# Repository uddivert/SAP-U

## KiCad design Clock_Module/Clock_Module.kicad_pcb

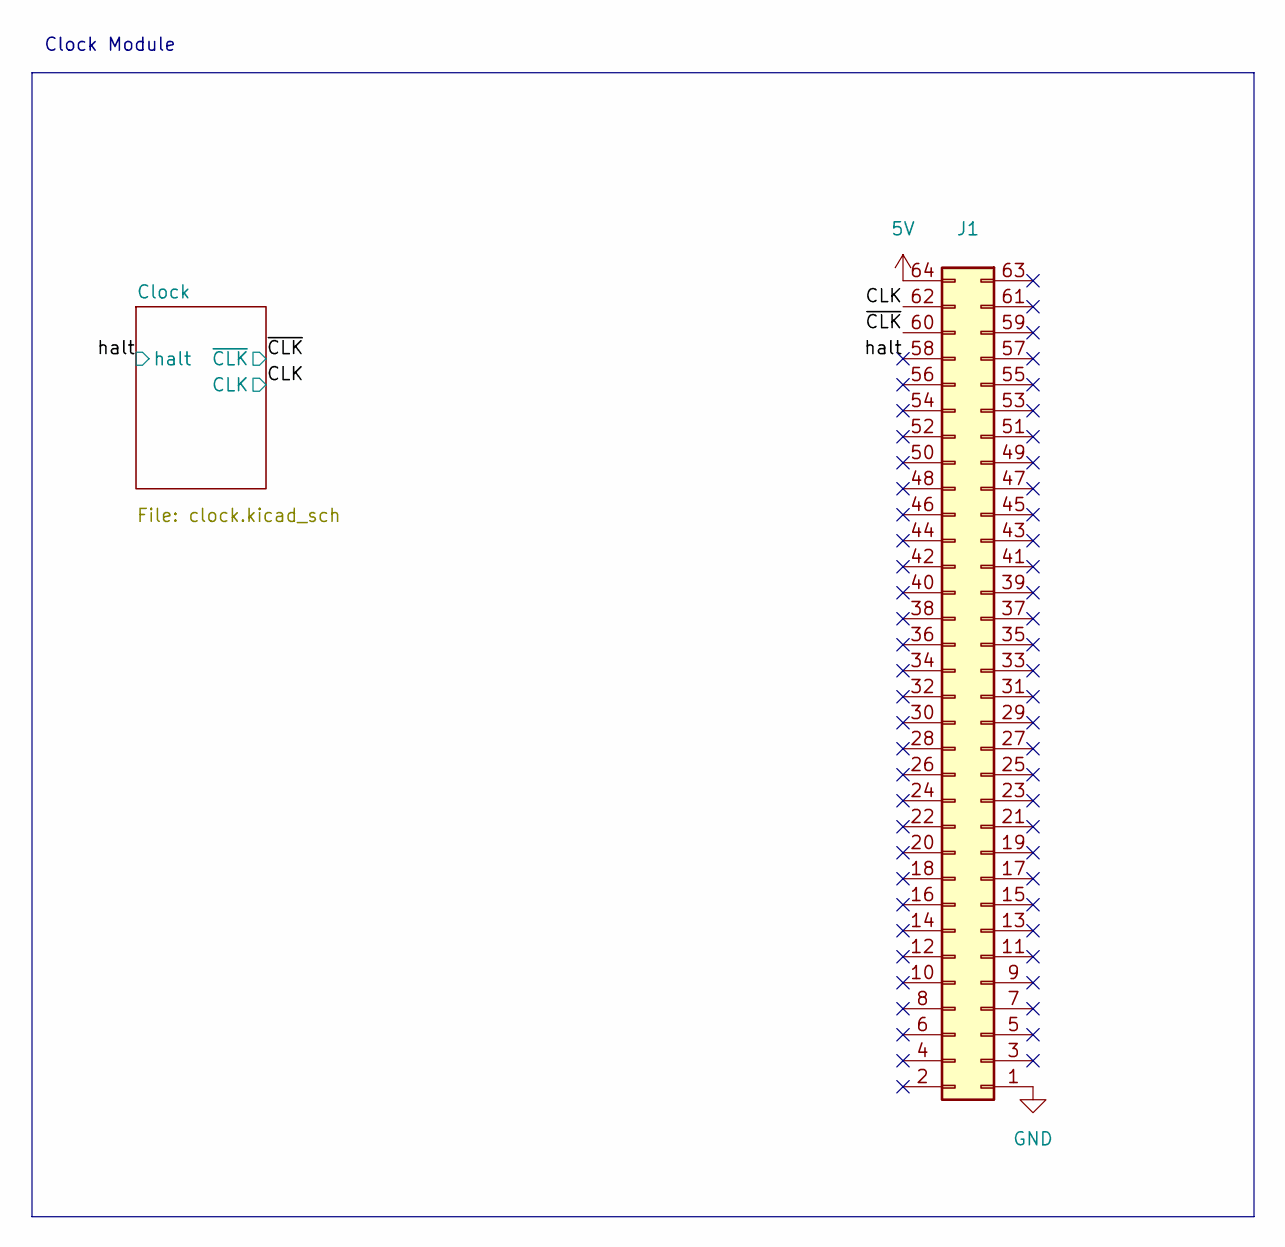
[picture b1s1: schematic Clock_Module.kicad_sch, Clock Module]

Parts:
J1: PC104-Standard

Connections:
5V: J1.64; also elsewhere on the board
/CLK: J1.62; also elsewhere on the board
/halt: J1.58; also elsewhere on the board
/~CLK: J1.60; also elsewhere on the board
GND: J1.1; also elsewhere on the board

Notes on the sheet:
Clock Module

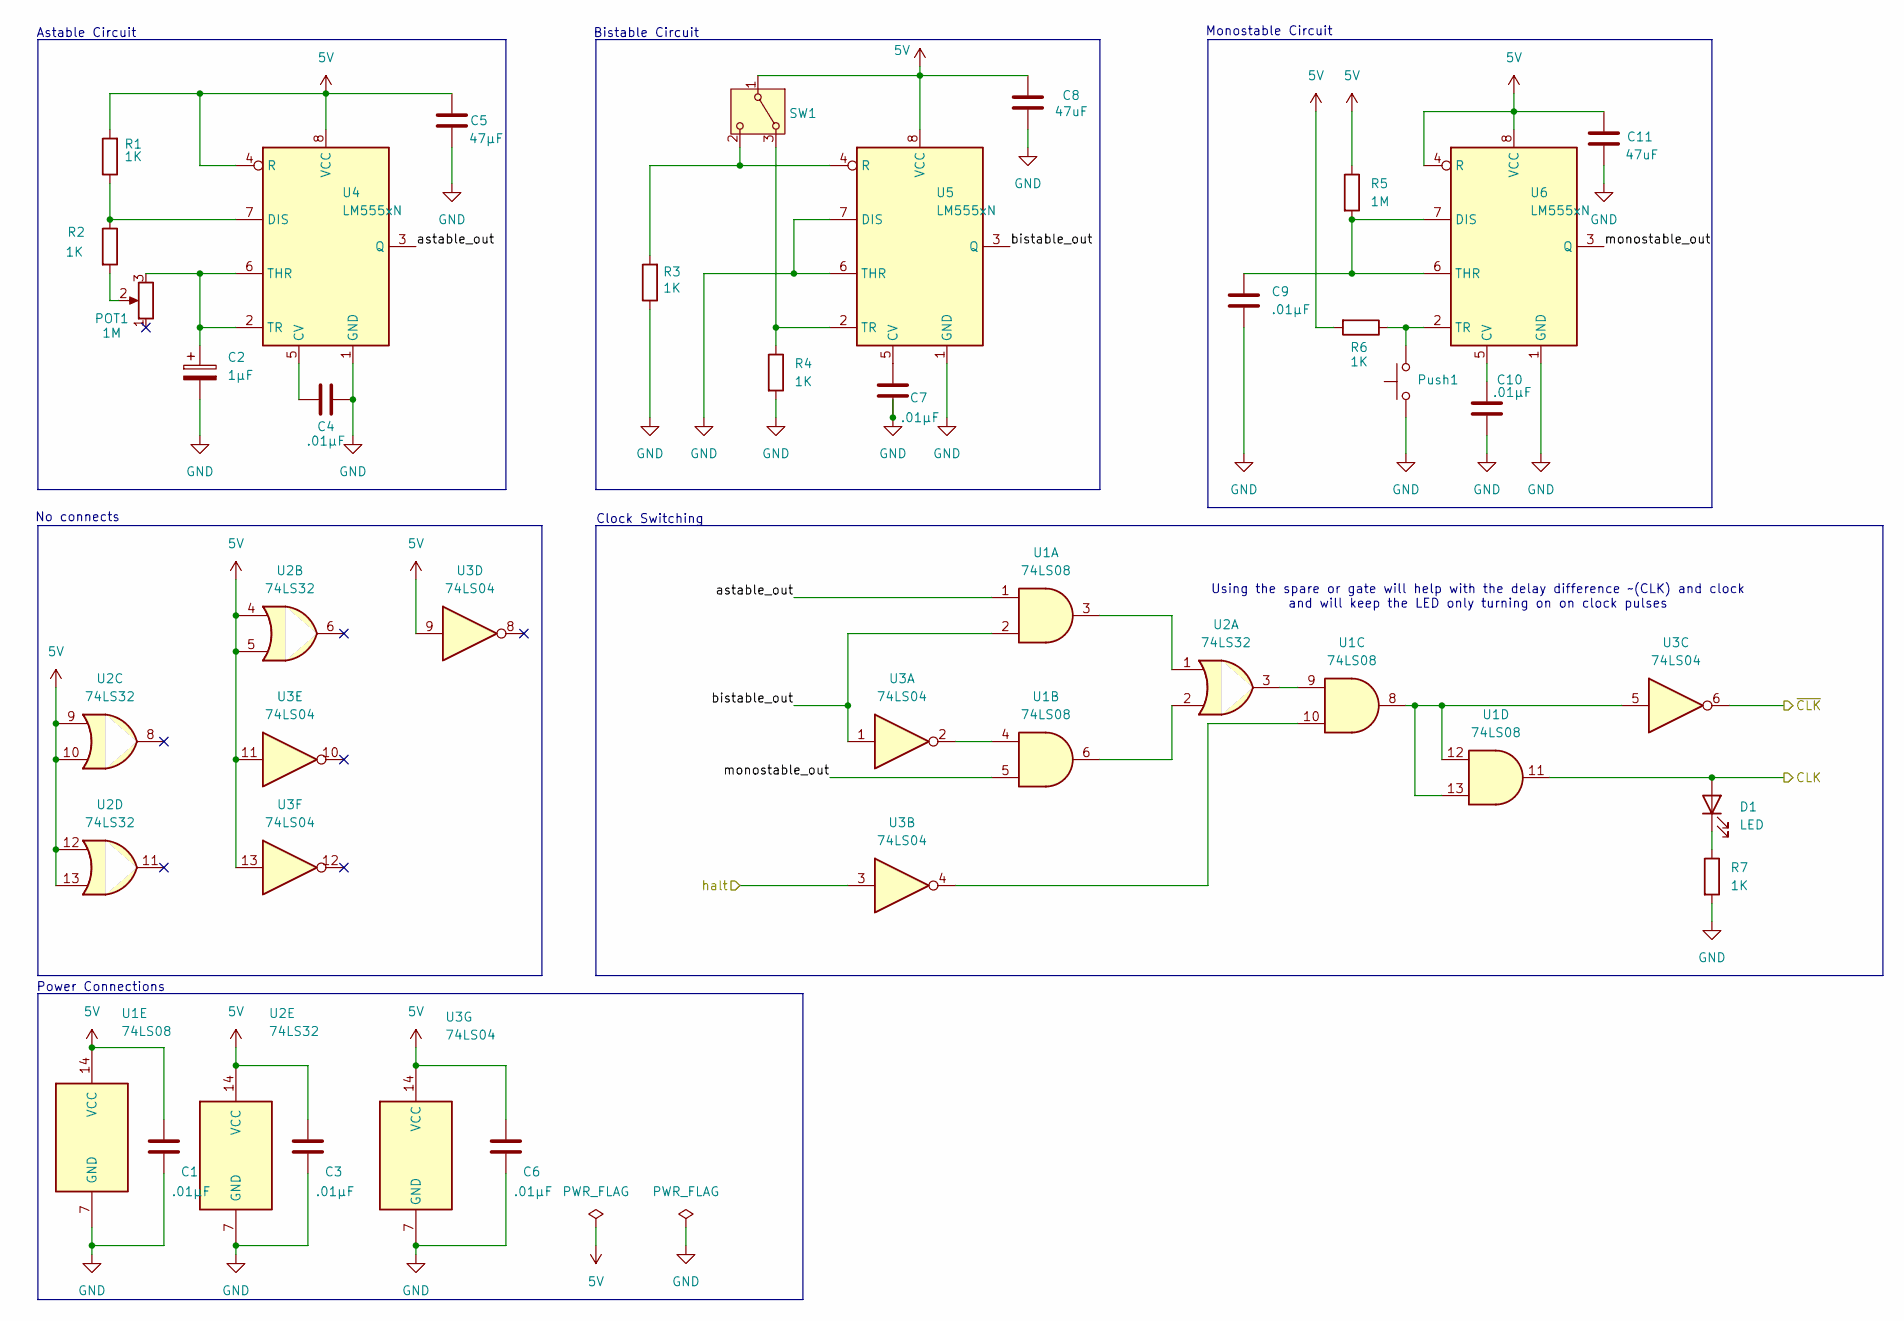
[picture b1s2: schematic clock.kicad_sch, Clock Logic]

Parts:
C1, C3, C4, C6, C7, C9, C10: .01µF; C_Disc_D5.0mm_W2.5mm_P2.50mm
C2: 1µF; C_Radial_D5.0mm_H11.0mm_P2.00mm
C5: 47µF; C_Disc_D5.0mm_W2.5mm_P2.50mm
C8, C11: 47uF; C_Disc_D5.0mm_W2.5mm_P2.50mm
D1: LED; LED_D5.0mm
POT1: 1M; Potentiometer_Bourns_3266Y_Vertical
Push1: SW_Push; SW_PUSH_6mm_H4.3mm
R1, R2, R3, R4, R6, R7: 1K; R_Axial_DIN0207_L6.3mm_D2.5mm_P5.08mm_Vertical
R5: 1M; R_Axial_DIN0207_L6.3mm_D2.5mm_P5.08mm_Vertical
SW1: Switch; SW_Slide-Jameco-SS-12E17-G020
U1: 74LS08; SN74LS08N
U2: 74LS32; SN74LS32N
U3: 74LS04; SN74LS04N
U4, U5, U6: LM555xN; DIP-8_W7.62mm

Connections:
5V: C1.2, C3.2, C5.1, C6.2, C8.2, C11.1, R1.2, R5.1, R6.2, SW1.1 (B), U1.14 (VCC), U2.4, U2.5, U2.9, U2.10, U2.12, U2.13, U2.14 (VCC), U3.9, U3.11, U3.13, U3.14 (VCC), U4.4 (R), U4.8 (VCC), U5.8 (VCC), U6.4 (R), U6.8 (VCC); also elsewhere on the board
/CLK: D1.2 (A), U1.11; also elsewhere on the board
/Clock/astable_out: U1.1, U4.3 (Q)
/Clock/bistable_out: U1.2, U3.1, U5.3 (Q)
/Clock/monostable_out: U1.5, U6.3 (Q)
/halt: U3.3; also elsewhere on the board
/~CLK: U3.6; also elsewhere on the board
GND: C1.1, C2.2, C3.1, C4.1, C5.2, C6.1, C7.1, C8.1, C9.1, C10.1, C11.2, Push1.1, R3.1, R4.2, R7.2, U1.7 (GND), U2.7 (GND), U3.7 (GND), U4.1 (GND), U5.1 (GND), U5.6 (THR), U5.7 (DIS), U6.1 (GND); also elsewhere on the board
unnamed: D1.1 (K), R7.1
unnamed: POT1.2, R2.2
unnamed: R4.1, SW1.3 (A), U5.2 (TR)
unnamed: R3.2, SW1.2 (C), U5.4 (R)
unnamed: U1.3, U2.1
unnamed: U1.4, U3.2
unnamed: U1.6, U2.2
unnamed: U1.9, U2.3
unnamed: U1.10, U3.4
unnamed: U1.8, U1.12, U1.13, U3.5
unnamed: C4.2, U4.5 (CV)
unnamed: R1.1, R2.1, U4.7 (DIS)
unnamed: C2.1, POT1.3, U4.2 (TR), U4.6 (THR)
unnamed: C7.2, U5.5 (CV)
unnamed: C10.2, U6.5 (CV)
unnamed: C9.2, R5.2, U6.6 (THR), U6.7 (DIS)
unnamed: Push1.2, R6.1, U6.2 (TR)

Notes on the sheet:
Astable Circuit
Power Connections
Bistable Circuit
Monostable Circuit
Clock Switching
No connects
Using the spare or gate will help with the delay difference ~(CLK) and clock and will keep the LED only turning on on clock pulses

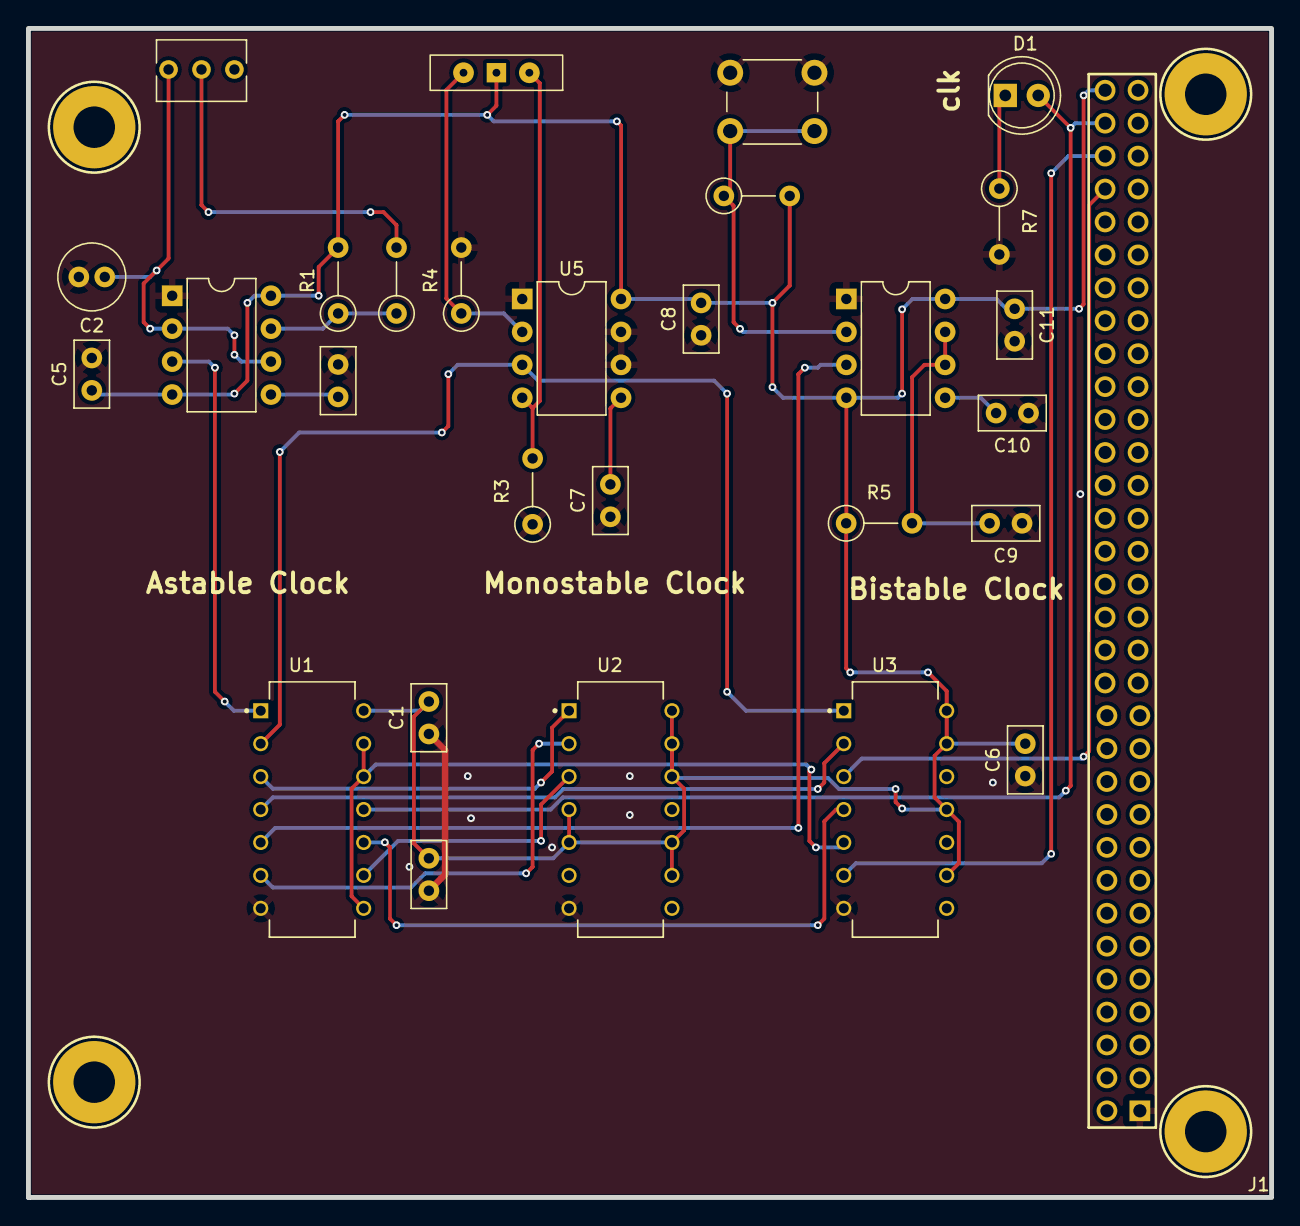
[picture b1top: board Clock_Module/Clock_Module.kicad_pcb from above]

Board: 2 copper layers, 95.9 x 90.2 mm, 29 parts (0 on the bottom side), 25 nets.

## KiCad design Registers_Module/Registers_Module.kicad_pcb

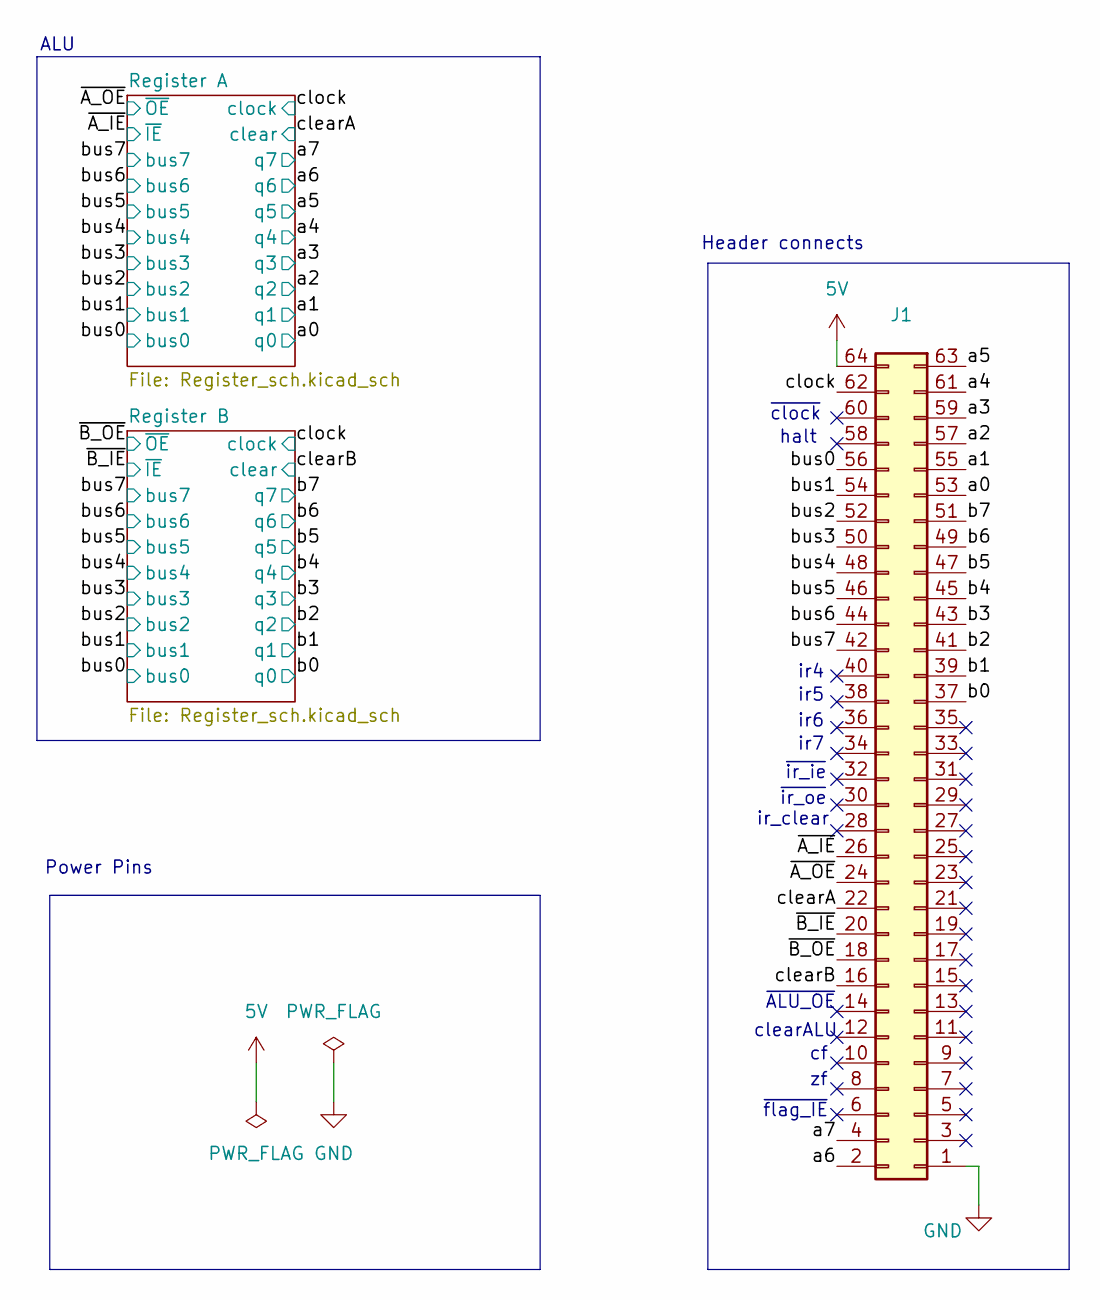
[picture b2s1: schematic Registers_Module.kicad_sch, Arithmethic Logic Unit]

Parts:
J1: PC104-Standard

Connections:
5V: J1.64; also elsewhere on the board
/a0: J1.53; also elsewhere on the board
/a1: J1.55; also elsewhere on the board
/a2: J1.57; also elsewhere on the board
/a3: J1.59; also elsewhere on the board
/a4: J1.61; also elsewhere on the board
/a5: J1.63; also elsewhere on the board
/a6: J1.2; also elsewhere on the board
/a7: J1.4; also elsewhere on the board
/b0: J1.37; also elsewhere on the board
/b1: J1.39; also elsewhere on the board
/b2: J1.41; also elsewhere on the board
/b3: J1.43; also elsewhere on the board
/b4: J1.45; also elsewhere on the board
/b5: J1.47; also elsewhere on the board
/b6: J1.49; also elsewhere on the board
/b7: J1.51; also elsewhere on the board
/bus0: J1.56; also elsewhere on the board
/bus1: J1.54; also elsewhere on the board
/bus2: J1.52; also elsewhere on the board
/bus3: J1.50; also elsewhere on the board
/bus4: J1.48; also elsewhere on the board
/bus5: J1.46; also elsewhere on the board
/bus6: J1.44; also elsewhere on the board
/bus7: J1.42; also elsewhere on the board
/clearA: J1.22; also elsewhere on the board
/clearB: J1.16; also elsewhere on the board
/clock: J1.62; also elsewhere on the board
/~A_IE: J1.26; also elsewhere on the board
/~A_OE: J1.24; also elsewhere on the board
/~B_IE: J1.20; also elsewhere on the board
/~B_OE: J1.18; also elsewhere on the board
GND: J1.1; also elsewhere on the board

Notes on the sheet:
ir5
ir6
~{ir_ie}
ALU
~{ir_oe}
~{ALU_OE}
ir_clear
halt
~{clock}
ir7
ir4
Header connects
Power Pins
~{flag_IE}
clearALU

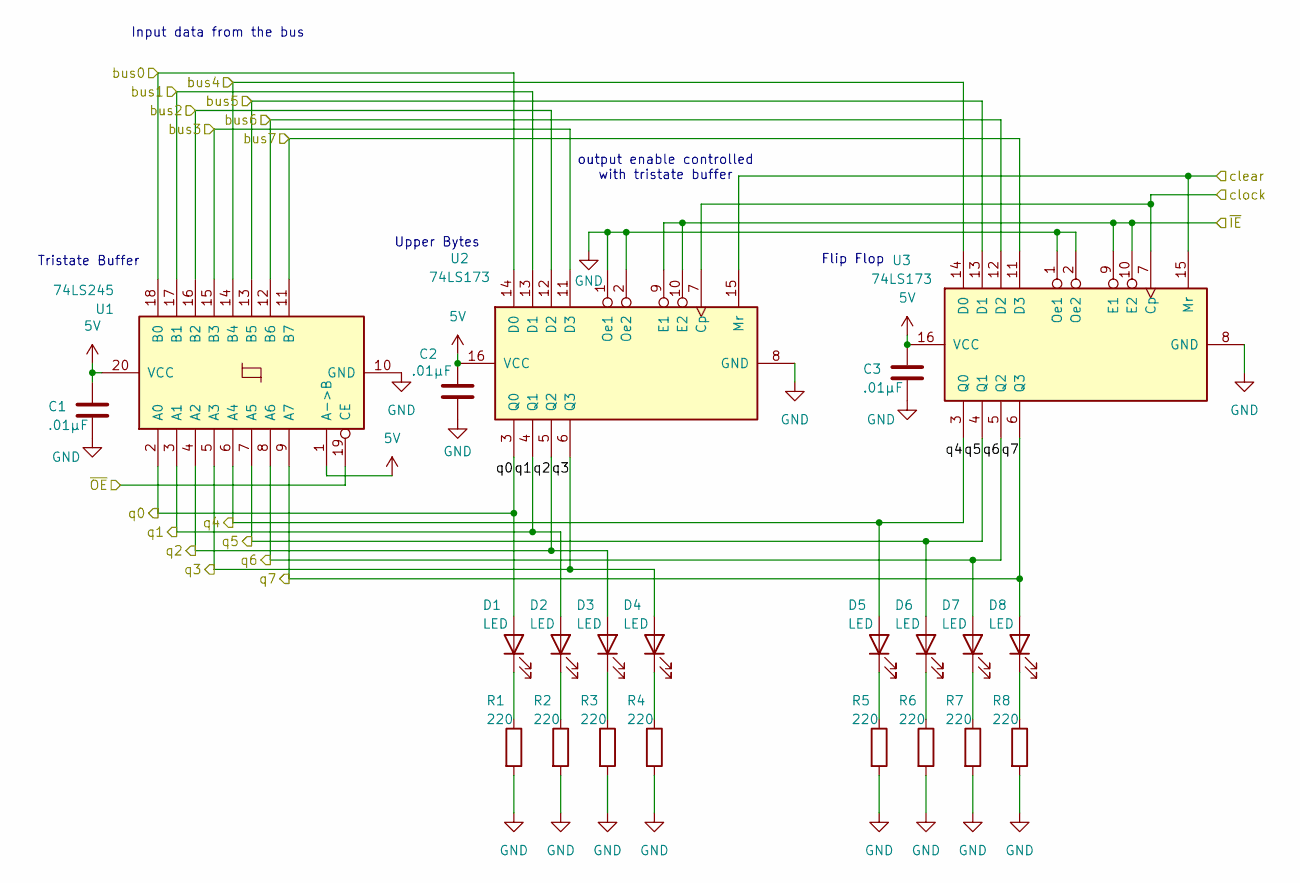
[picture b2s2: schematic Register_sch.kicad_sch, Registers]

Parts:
C1, C2, C3: .01µF; C_Disc_D5.0mm_W2.5mm_P2.50mm
D1, D2, D3, D4, D5, D6, D7, D8: LED; LED_D5.0mm
R1, R2, R3, R4, R5, R6, R7, R8: 220; R_Axial_DIN0207_L6.3mm_D2.5mm_P5.08mm_Vertical
U1: 74LS245; DIP-20_W7.62mm
U2, U3: 74LS173; DIP-16_W7.62mm

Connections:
5V: C1.2, C2.2, C3.2, U1.1 (A->B), U1.20 (VCC), U2.16 (VCC), U3.16 (VCC); also elsewhere on the board
/a0: D1.2 (A), U1.2 (A0), U2.3 (Q0); also elsewhere on the board
/a1: D2.2 (A), U1.3 (A1), U2.4 (Q1); also elsewhere on the board
/a2: D3.2 (A), U1.4 (A2), U2.5 (Q2); also elsewhere on the board
/a3: D4.2 (A), U1.5 (A3), U2.6 (Q3); also elsewhere on the board
/a4: D5.2 (A), U1.6 (A4), U3.3 (Q0); also elsewhere on the board
/a5: D6.2 (A), U1.7 (A5), U3.4 (Q1); also elsewhere on the board
/a6: D7.2 (A), U1.8 (A6), U3.5 (Q2); also elsewhere on the board
/a7: D8.2 (A), U1.9 (A7), U3.6 (Q3); also elsewhere on the board
/bus0: U1.18 (B0), U2.14 (D0); also elsewhere on the board
/bus1: U1.17 (B1), U2.13 (D1); also elsewhere on the board
/bus2: U1.16 (B2), U2.12 (D2); also elsewhere on the board
/bus3: U1.15 (B3), U2.11 (D3); also elsewhere on the board
/bus4: U1.14 (B4), U3.14 (D0); also elsewhere on the board
/bus5: U1.13 (B5), U3.13 (D1); also elsewhere on the board
/bus6: U1.12 (B6), U3.12 (D2); also elsewhere on the board
/bus7: U1.11 (B7), U3.11 (D3); also elsewhere on the board
/clearA: U2.15 (Mr), U3.15 (Mr); also elsewhere on the board
/clock: U2.7 (Cp), U3.7 (Cp); also elsewhere on the board
/~A_IE: U2.9 (E1), U2.10 (E2), U3.9 (E1), U3.10 (E2); also elsewhere on the board
/~A_OE: U1.19 (CE); also elsewhere on the board
GND: C1.1, C2.1, C3.1, R1.2, R2.2, R3.2, R4.2, R5.2, R6.2, R7.2, R8.2, U1.10 (GND), U2.1 (Oe1), U2.2 (Oe2), U2.8 (GND), U3.1 (Oe1), U3.2 (Oe2), U3.8 (GND); also elsewhere on the board
unnamed: D1.1 (K), R1.1
unnamed: D2.1 (K), R2.1
unnamed: D3.1 (K), R3.1
unnamed: D4.1 (K), R4.1
unnamed: D5.1 (K), R5.1
unnamed: D6.1 (K), R6.1
unnamed: D7.1 (K), R7.1
unnamed: D8.1 (K), R8.1

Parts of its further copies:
C12, C13, C14: .01µF; C_Disc_D5.0mm_W2.5mm_P2.50mm
D17, D18, D19, D20, D21, D22, D23, D24: LED; LED_D5.0mm
R17, R18, R19, R20, R21, R22, R23, R24: 220; R_Axial_DIN0207_L6.3mm_D2.5mm_P5.08mm_Vertical
U12: 74LS245; DIP-20_W7.62mm
U13, U14: 74LS173; DIP-16_W7.62mm

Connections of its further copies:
5V: C12.2, C13.2, C14.2, U12.1 (A->B), U12.20 (VCC), U13.16 (VCC), U14.16 (VCC); also elsewhere on the board
/b0: D17.2 (A), U12.2 (A0), U13.3 (Q0); also elsewhere on the board
/b1: D18.2 (A), U12.3 (A1), U13.4 (Q1); also elsewhere on the board
/b2: D19.2 (A), U12.4 (A2), U13.5 (Q2); also elsewhere on the board
/b3: D20.2 (A), U12.5 (A3), U13.6 (Q3); also elsewhere on the board
/b4: D21.2 (A), U12.6 (A4), U14.3 (Q0); also elsewhere on the board
/b5: D22.2 (A), U12.7 (A5), U14.4 (Q1); also elsewhere on the board
/b6: D23.2 (A), U12.8 (A6), U14.5 (Q2); also elsewhere on the board
/b7: D24.2 (A), U12.9 (A7), U14.6 (Q3); also elsewhere on the board
/bus0: U12.18 (B0), U13.14 (D0); also elsewhere on the board
/bus1: U12.17 (B1), U13.13 (D1); also elsewhere on the board
/bus2: U12.16 (B2), U13.12 (D2); also elsewhere on the board
/bus3: U12.15 (B3), U13.11 (D3); also elsewhere on the board
/bus4: U12.14 (B4), U14.14 (D0); also elsewhere on the board
/bus5: U12.13 (B5), U14.13 (D1); also elsewhere on the board
/bus6: U12.12 (B6), U14.12 (D2); also elsewhere on the board
/bus7: U12.11 (B7), U14.11 (D3); also elsewhere on the board
/clearB: U13.15 (Mr), U14.15 (Mr); also elsewhere on the board
/clock: U13.7 (Cp), U14.7 (Cp); also elsewhere on the board
/~B_IE: U13.9 (E1), U13.10 (E2), U14.9 (E1), U14.10 (E2); also elsewhere on the board
/~B_OE: U12.19 (CE); also elsewhere on the board
GND: C12.1, C13.1, C14.1, R17.2, R18.2, R19.2, R20.2, R21.2, R22.2, R23.2, R24.2, U12.10 (GND), U13.1 (Oe1), U13.2 (Oe2), U13.8 (GND), U14.1 (Oe1), U14.2 (Oe2), U14.8 (GND); also elsewhere on the board
unnamed: D17.1 (K), R17.1
unnamed: D18.1 (K), R18.1
unnamed: D19.1 (K), R19.1
unnamed: D20.1 (K), R20.1
unnamed: D21.1 (K), R21.1
unnamed: D22.1 (K), R22.1
unnamed: D23.1 (K), R23.1
unnamed: D24.1 (K), R24.1

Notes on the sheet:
Upper Bytes
Flip Flop
output enable controlled with tristate buffer
Input data from the bus
Tristate Buffer

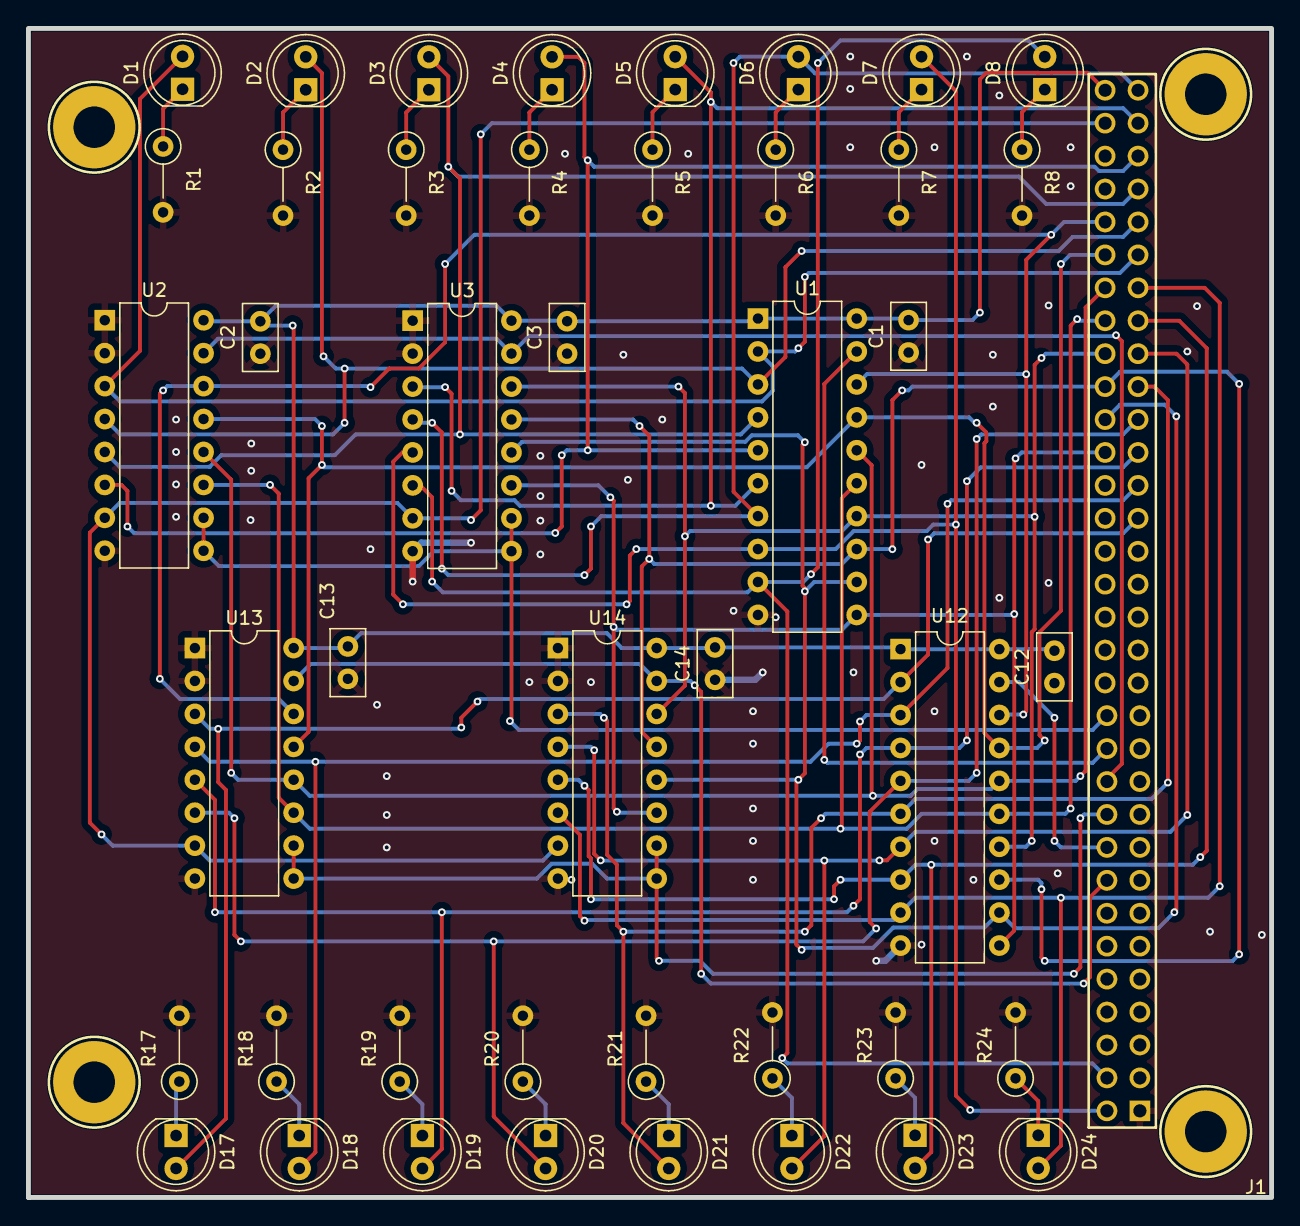
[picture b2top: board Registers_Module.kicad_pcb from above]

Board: 2 copper layers, 95.9 x 90.2 mm, 45 parts (0 on the bottom side), 49 nets.

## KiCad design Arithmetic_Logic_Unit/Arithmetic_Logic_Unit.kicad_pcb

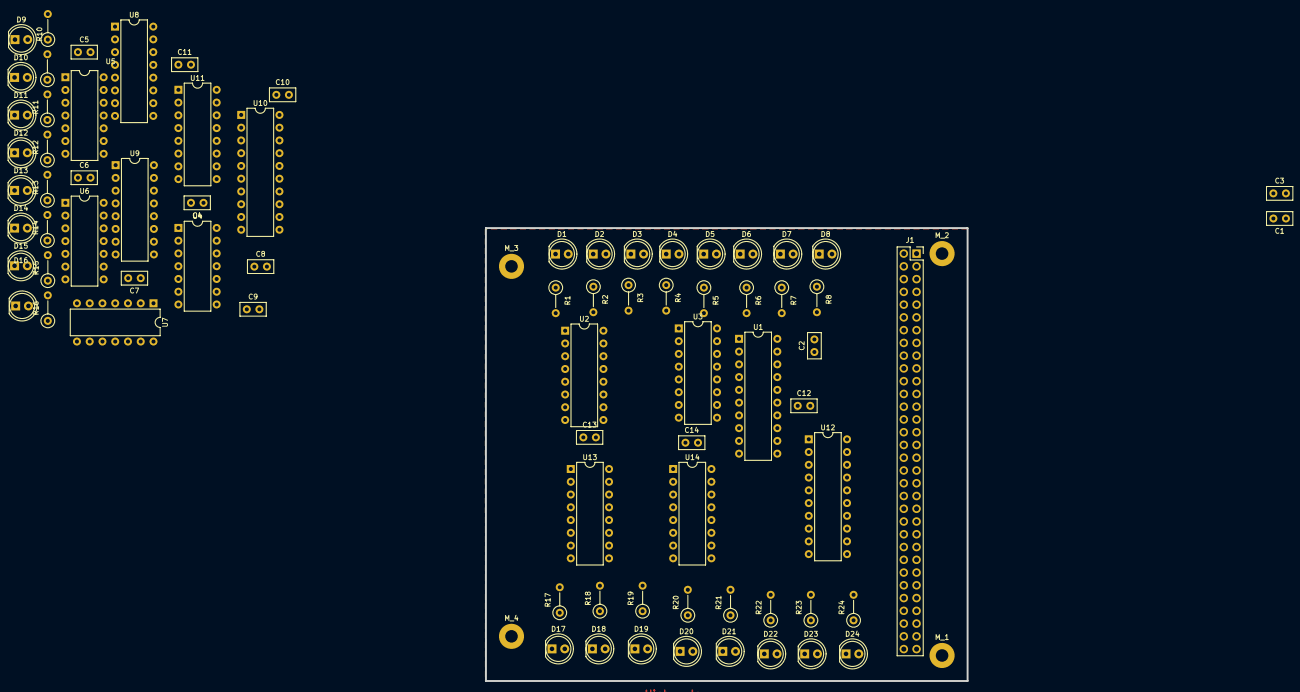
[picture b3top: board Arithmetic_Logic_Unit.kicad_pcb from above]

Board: 2 copper layers, 95.9 x 90.2 mm, 81 parts (0 on the bottom side), 88 nets, no tracks yet.

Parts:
C1, C2, C3, C4, C5, C6, C7, C8, C9, C10, C11, C12, C13, C14: .01µF; C_Disc_D5.0mm_W2.5mm_P2.50mm
D1, D2, D3, D4, D5, D6, D7, D8, D9, D10, D11, D12, D13, D14, D15, D16, D17, D18, D19, D20, D21, D22, D23, D24: LED; LED_D5.0mm
J1: PC104; PinSocket_2x32_P2.54mm_Vertical
M_1, M_2, M_3, M_4: MountingHole_2.5mm_Pad
R1, R2, R3, R4, R5, R6, R7, R8, R9, R10, R11, R12, R13, R14, R15, R16, R17, R18, R19, R20, R21, R22, R23, R24: 220; R_Axial_DIN0207_L6.3mm_D2.5mm_P5.08mm_Vertical
U1, U10, U12: 74LS245; DIP-20_W7.62mm
U2, U3, U11, U13, U14: 74LS173; DIP-16_W7.62mm
U4: 74LS08; DIP-14_W7.62mm
U5, U6: 74LS86; DIP-14_W7.62mm
U7: 74LS02; DIP-14_W7.62mm
U8, U9: 74LS283; DIP-16_W7.62mm

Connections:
5V: C1.2, C2.2, C3.2, C4.2, C5.2, C6.2, C7.2, C8.2, C9.2, C10.2, C11.2, C12.2, C13.2, C14.2, J1.36, J1.62, U1.1 (A->B), U1.20 (VCC), U2.16 (VCC), U3.16 (VCC), U4.14 (VCC), U5.14 (VCC), U6.14 (VCC), U7.14 (VCC), U8.16 (VCC), U9.16 (VCC), U10.1 (A->B), U10.20 (VCC), U11.16 (VCC), U12.1 (A->B), U12.20 (VCC), U13.16 (VCC), U14.16 (VCC)
/ALU/a0: D1.2 (A), U1.2 (A0), U2.3 (Q0), U9.12 (A4)
/ALU/a1: D2.2 (A), U1.3 (A1), U2.4 (Q1), U9.14 (A3)
/ALU/a2: D3.2 (A), U1.4 (A2), U2.5 (Q2), U9.3 (A2)
/ALU/a3: D4.2 (A), U1.5 (A3), U2.6 (Q3), U9.5 (A1)
/ALU/a4: D5.2 (A), U1.6 (A4), U3.3 (Q0), U8.12 (A4)
/ALU/a5: D6.2 (A), U1.7 (A5), U3.4 (Q1), U8.14 (A3)
/ALU/a6: D7.2 (A), U1.8 (A6), U3.5 (Q2), U8.3 (A2)
/ALU/a7: D8.2 (A), U1.9 (A7), U3.6 (Q3), U8.5 (A1)
/ALU/b0: D17.2 (A), U6.12, U12.2 (A0), U13.3 (Q0)
/ALU/b1: D18.2 (A), U6.9, U12.3 (A1), U13.4 (Q1)
/ALU/b2: D19.2 (A), U6.4, U12.4 (A2), U13.5 (Q2)
/ALU/b3: D20.2 (A), U6.1, U12.5 (A3), U13.6 (Q3)
/ALU/b4: D21.2 (A), U5.12, U12.6 (A4), U14.3 (Q0)
/ALU/b5: D22.2 (A), U5.9, U12.7 (A5), U14.4 (Q1)
/ALU/b6: D23.2 (A), U5.4, U12.8 (A6), U14.5 (Q2)
/ALU/b7: D24.2 (A), U5.1, U12.9 (A7), U14.6 (Q3)
/ALU/carry_connector: U8.7 (C0), U9.9 (C4)
/ALU/s0: D9.2 (A), U7.12, U9.10 (S4), U10.9 (A7)
/ALU/s1: D10.2 (A), U7.11, U9.13 (S3), U10.8 (A6)
/ALU/s2: D11.2 (A), U7.9, U9.1 (S2), U10.7 (A5)
/ALU/s3: D12.2 (A), U7.8, U9.4 (S1), U10.6 (A4)
/ALU/s4: D13.2 (A), U7.6, U8.10 (S4), U10.5 (A3)
/ALU/s5: D14.2 (A), U7.5, U8.13 (S3), U10.4 (A2)
/ALU/s6: D15.2 (A), U7.3, U8.1 (S2), U10.3 (A1)
/ALU/s7: D16.2 (A), U7.2, U8.4 (S1), U10.2 (A0)
/ALU/~b0: U6.11, U9.11 (B4)
/ALU/~b1: U6.8, U9.15 (B3)
/ALU/~b2: U6.6, U9.2 (B2)
/ALU/~b3: U6.3, U9.6 (B1)
/ALU/~b4: U5.11, U8.11 (B4)
/ALU/~b5: U5.8, U8.15 (B3)
/ALU/~b6: U5.6, U8.2 (B2)
/ALU/~b7: U5.3, U8.6 (B1)
/bus0: J1.9, U1.18 (B0), U2.14 (D0), U10.11 (B7), U12.18 (B0), U13.14 (D0)
/bus1: J1.8, U1.17 (B1), U2.13 (D1), U10.12 (B6), U12.17 (B1), U13.13 (D1)
/bus2: J1.7, U1.16 (B2), U2.12 (D2), U10.13 (B5), U12.16 (B2), U13.12 (D2)
/bus3: J1.6, U1.15 (B3), U2.11 (D3), U10.14 (B4), U12.15 (B3), U13.11 (D3)
/bus4: J1.5, U1.14 (B4), U3.14 (D0), U10.15 (B3), U12.14 (B4), U14.14 (D0)
/bus5: J1.4, U1.13 (B5), U3.13 (D1), U10.16 (B2), U12.13 (B5), U14.13 (D1)
/bus6: J1.3, U1.12 (B6), U3.12 (D2), U10.17 (B1), U12.12 (B6), U14.12 (D2)
/bus7: J1.2, U1.11 (B7), U3.11 (D3), U10.18 (B0), U12.11 (B7), U14.11 (D3)
/cf: J1.17, U11.3 (Q0)
/clear: J1.19, U11.15 (Mr)
/clearA: J1.15, U2.15 (Mr), U3.15 (Mr)
/clearB: J1.16, U13.15 (Mr), U14.15 (Mr)
/clock: J1.45, U2.7 (Cp), U3.7 (Cp), U11.7 (Cp), U13.7 (Cp), U14.7 (Cp)
/en_sub: J1.13, U5.2, U5.5, U5.10, U5.13, U6.2, U6.5, U6.10, U6.13, U9.7 (C0)
/fi: J1.20, U11.9 (E1), U11.10 (E2)
/zf: J1.18, U11.4 (Q1)
/~ALU_OE: J1.28, U10.19 (CE)
/~A_IE: J1.26, U2.9 (E1), U2.10 (E2), U3.9 (E1), U3.10 (E2)
/~A_OE: J1.31, U1.19 (CE)
/~B_IE: J1.27, U13.9 (E1), U13.10 (E2), U14.9 (E1), U14.10 (E2)
/~B_OE: J1.30, U12.19 (CE)
GND: C1.1, C2.1, C3.1, C4.1, C5.1, C6.1, C7.1, C8.1, C9.1, C10.1, C11.1, C12.1, C13.1, C14.1, J1.32, J1.33, J1.34, J1.64, M_1.1, M_2.1, M_3.1, M_4.1, R1.2, R2.2, R3.2, R4.2, R5.2, R6.2, R7.2, R8.2, R9.2, R10.2, R11.2, R12.2, R13.2, R14.2, R15.2, R16.2, R17.2, R18.2, R19.2, R20.2, R21.2, R22.2, R23.2, R24.2, U1.10 (GND), U2.1 (Oe1), U2.2 (Oe2), U2.8 (GND), U3.1 (Oe1), U3.2 (Oe2), U3.8 (GND), U4.7 (GND), U4.12, U4.13, U5.7 (GND), U6.7 (GND), U7.7 (GND), U8.8 (GND), U9.8 (GND), U10.10 (GND), U11.1 (Oe1), U11.2 (Oe2), U11.8 (GND), U12.10 (GND), U13.1 (Oe1), U13.2 (Oe2), U13.8 (GND), U14.1 (Oe1), U14.2 (Oe2), U14.8 (GND)
unnamed: D1.1 (K), R1.1
unnamed: D2.1 (K), R2.1
unnamed: D3.1 (K), R3.1
unnamed: D4.1 (K), R4.1
unnamed: D5.1 (K), R5.1
unnamed: D6.1 (K), R6.1
unnamed: D7.1 (K), R7.1
unnamed: D8.1 (K), R8.1
unnamed: D9.1 (K), R9.1
unnamed: D10.1 (K), R10.1
unnamed: D11.1 (K), R11.1
unnamed: D12.1 (K), R12.1
unnamed: D13.1 (K), R13.1
unnamed: D14.1 (K), R14.1
unnamed: D15.1 (K), R15.1
unnamed: D16.1 (K), R16.1
unnamed: D17.1 (K), R17.1
unnamed: D18.1 (K), R18.1
unnamed: D19.1 (K), R19.1
unnamed: D20.1 (K), R20.1
unnamed: D21.1 (K), R21.1
unnamed: D22.1 (K), R22.1
unnamed: D23.1 (K), R23.1
unnamed: D24.1 (K), R24.1
unnamed: U4.1, U7.1
unnamed: U4.2, U7.4
unnamed: U4.3, U4.9
unnamed: U4.4, U7.10
unnamed: U4.5, U7.13
unnamed: U4.6, U4.10
unnamed: U8.9 (C4), U11.14 (D0)
unnamed: U4.8, U11.13 (D1)

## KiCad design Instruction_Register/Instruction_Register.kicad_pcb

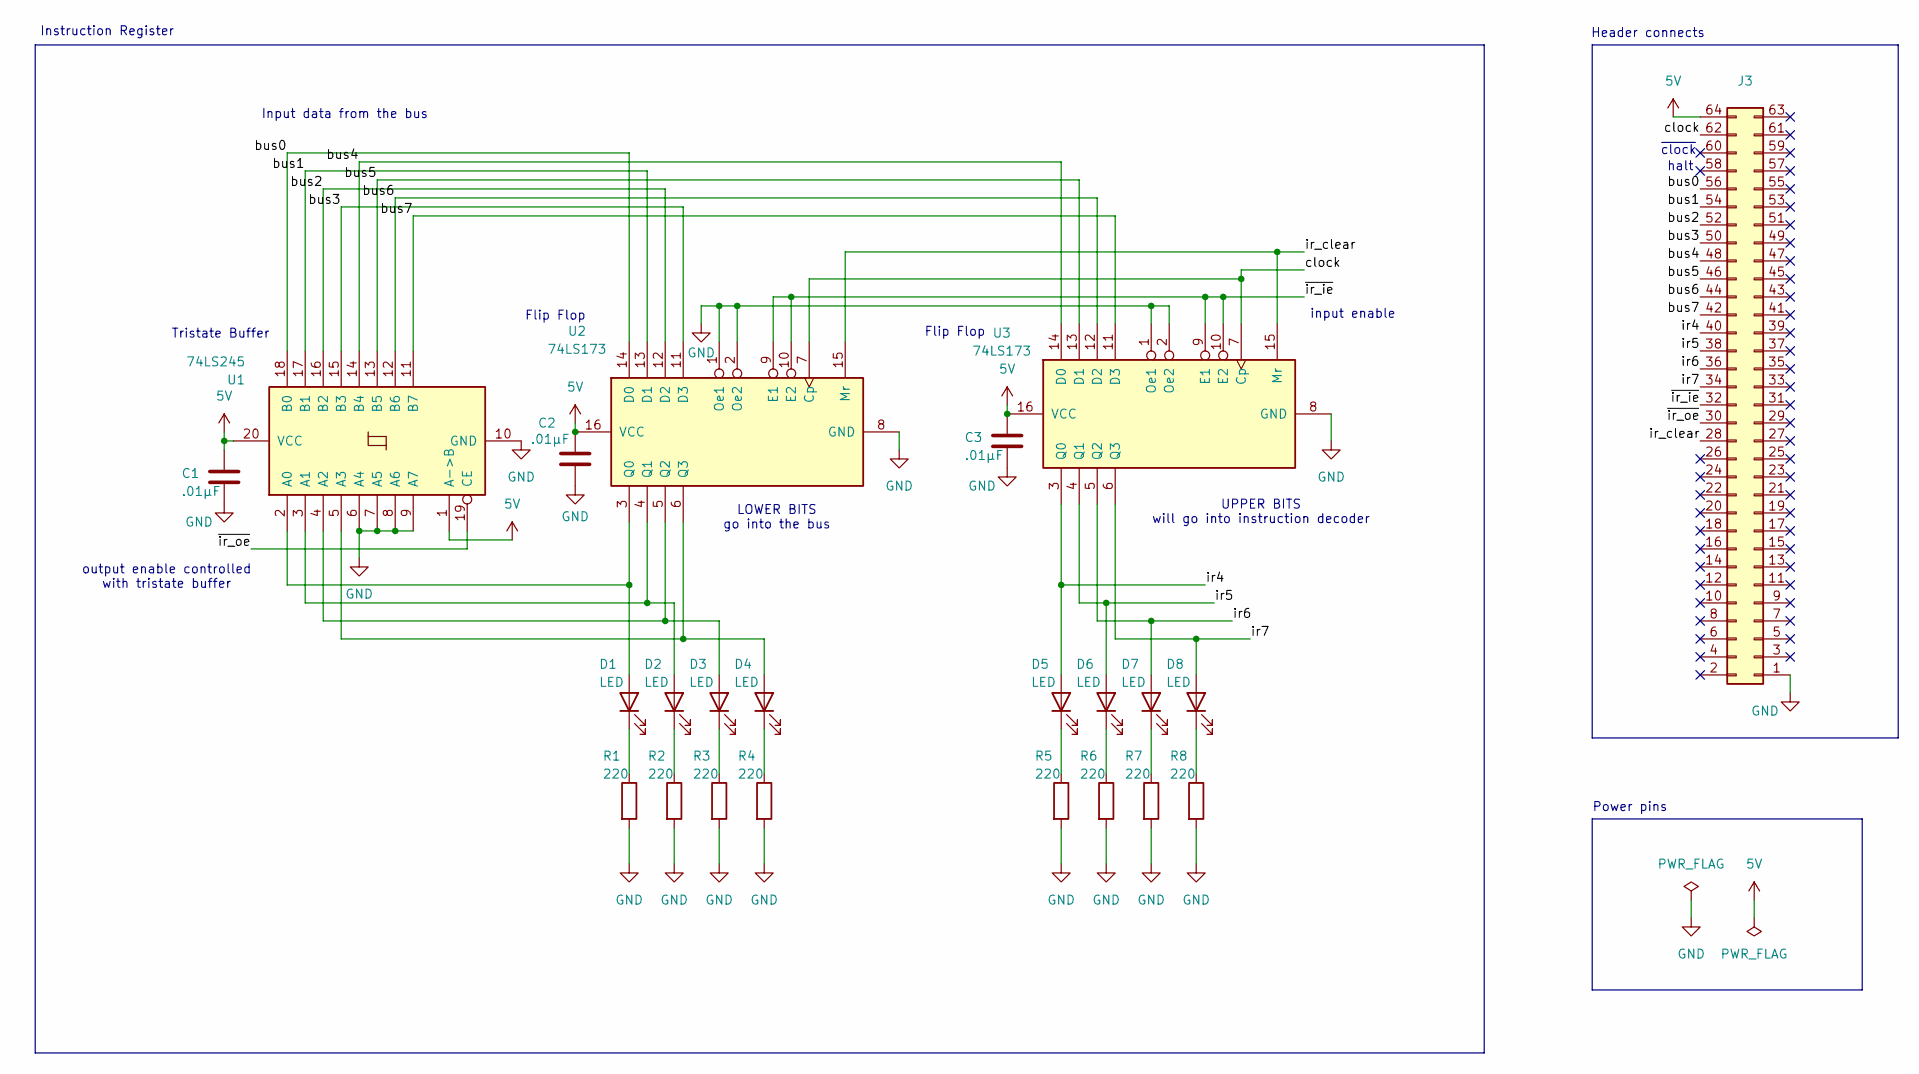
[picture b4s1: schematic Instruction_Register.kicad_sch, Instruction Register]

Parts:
C1, C2, C3: .01µF; C_Disc_D5.0mm_W2.5mm_P2.50mm
D1, D2, D3, D4, D5, D6, D7, D8: LED; LED_D5.0mm
J3: PC104-Standard
R1, R2, R3, R4, R5, R6, R7, R8: 220; R_Axial_DIN0207_L6.3mm_D2.5mm_P5.08mm_Vertical
U1: 74LS245; DIP-20_W7.62mm
U2, U3: 74LS173; DIP-16_W7.62mm

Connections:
5V: C1.2, C2.2, C3.2, J3.64, U1.1 (A->B), U1.20 (VCC), U2.16 (VCC), U3.16 (VCC)
/bus0: J3.56, U1.18 (B0), U2.14 (D0)
/bus1: J3.54, U1.17 (B1), U2.13 (D1)
/bus2: J3.52, U1.16 (B2), U2.12 (D2)
/bus3: J3.50, U1.15 (B3), U2.11 (D3)
/bus4: J3.48, U1.14 (B4), U3.14 (D0)
/bus5: J3.46, U1.13 (B5), U3.13 (D1)
/bus6: J3.44, U1.12 (B6), U3.12 (D2)
/bus7: J3.42, U1.11 (B7), U3.11 (D3)
/clock: J3.62, U2.7 (Cp), U3.7 (Cp)
/ir4: D5.2 (A), J3.40, U3.3 (Q0)
/ir5: D6.2 (A), J3.38, U3.4 (Q1)
/ir6: D7.2 (A), J3.36, U3.5 (Q2)
/ir7: D8.2 (A), J3.34, U3.6 (Q3)
/ir_clear: J3.28, U2.15 (Mr), U3.15 (Mr)
/~ir_ie: J3.32, U2.9 (E1), U2.10 (E2), U3.9 (E1), U3.10 (E2)
/~ir_oe: J3.30, U1.19 (CE)
GND: C1.1, C2.1, C3.1, J3.1, R1.2, R2.2, R3.2, R4.2, R5.2, R6.2, R7.2, R8.2, U1.6 (A4), U1.7 (A5), U1.8 (A6), U1.9 (A7), U1.10 (GND), U2.1 (Oe1), U2.2 (Oe2), U2.8 (GND), U3.1 (Oe1), U3.2 (Oe2), U3.8 (GND)
unnamed: D1.2 (A), U1.2 (A0), U2.3 (Q0)
unnamed: D1.1 (K), R1.1
unnamed: D2.2 (A), U1.3 (A1), U2.4 (Q1)
unnamed: D2.1 (K), R2.1
unnamed: D3.2 (A), U1.4 (A2), U2.5 (Q2)
unnamed: D3.1 (K), R3.1
unnamed: D4.2 (A), U1.5 (A3), U2.6 (Q3)
unnamed: D4.1 (K), R4.1
unnamed: D5.1 (K), R5.1
unnamed: D6.1 (K), R6.1
unnamed: D7.1 (K), R7.1
unnamed: D8.1 (K), R8.1

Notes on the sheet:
UPPER BITS will go into instruction decoder
input enable
Flip Flop
Instruction Register
Power pins
~{clock}
Header connects
halt
output enable controlled with tristate buffer
LOWER BITS go into the bus
Input data from the bus
Tristate Buffer
